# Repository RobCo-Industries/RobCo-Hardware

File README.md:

# RobCo-Hardware

Status: proposals. Nothing here is built, tested or validated on hardware.

This repository holds the board designs for the RobCo suite. Two boards are planned: a terminal controller HAT and a Pip-Boy HAT for the Raspberry Pi. Neither exists yet.

## Boards

| Folder | Board | Status |
|---|---|---|
| `toy/` | Toolchain test: a 3-pin header, a resistor and an LED | Test bed. Schematic, routed board, renders. |
| `toy2/` | Hierarchy test: an expander, a clock and eight LED channels on two sheets | Test bed. Schematic only. |
| `terminal-controller/` | Terminal controller HAT | Schematic drawn, ERC clean. The parts do not fit the HAT yet. See its [README](terminal-controller/README.md). |
| `pipboy-hat/` | Pip-Boy HAT: display, keys, dial, speaker, clock and holotape slot for a Pi Zero | Schematic drawn, ERC clean. Holotape slot added to the spec and schematic. Board not started. See its [README](pipboy-hat/README.md). |

The terminal controller spec is in [terminal-controller/spec/SPEC.md](terminal-controller/spec/SPEC.md), with its bring-up checklist in [BRINGUP.md](terminal-controller/spec/BRINGUP.md) and its header map in [pins.yaml](terminal-controller/spec/pins.yaml). The Pip-Boy HAT spec is in [pipboy-hat/spec/SPEC.md](pipboy-hat/spec/SPEC.md), with [BRINGUP.md](pipboy-hat/spec/BRINGUP.md) and [pins.yaml](pipboy-hat/spec/pins.yaml).

## Safety

The boards are for low voltage only, 5 to 24 V. They never switch mains. Mains loads need an external, rated relay module.

## Tools

- KiCad 10.0.8 with `kicad-cli`. On macOS the scripts find it in `/Applications/KiCad`. On Linux they look in `/usr/bin` and `/usr/share/kicad`.
- The Python that ships with KiCad. It can import `pcbnew`, which the board generator needs.
- Python 3.9 or later with `pytest` for the tests. `tools/build.sh test` makes a venv under `build/`.
- RobCo-Core, for the pin check. Set `ROBCO_BOARD_SUPPORT` to the path of its `docs/spec/BOARD_SUPPORT.md`. The script also finds a RobCo-Core clone next to this one, or two levels up from a worktree.

## Generate, check and export a board

```sh
tools/build.sh gen toy     # rewrite toy/kicad/ from toy/gen/
tools/build.sh check toy   # regen-diff, ERC, pin check, DRC
tools/build.sh out toy     # PDF, SVG, netlist, BOM, renders, gerbers, drill
tools/build.sh test        # Python tests
```

Every output goes to `build/<board>/`. Run `tools/build.sh` with no command for the full list and the variables it reads.

`check` fails when:

- the committed KiCad files differ from a fresh generation,
- ERC finds any violation,
- a header pin in the netlist differs from `spec/pins.yaml`, or `pins.yaml` gives a GPIO another use than the software,
- the pin table in `spec/SPEC.md` differs from the one `tools/gen_pin_table.py` writes from `pins.yaml`,
- a board whose `board.env` names netlist tests with `NETTEST` fails one of them,
- DRC finds a violation, on a board whose `board.env` says `ROUTED=yes`. On other boards DRC only writes a report.

A board with no board file yet is checked as a schematic. `check` runs the regen-diff, ERC and the pin checks, and prints a line for each step it skips. A board with no generator yet gets the pin checks only. When the owner routes a board, `board.env` says `OWNER_ROUTED=yes`. The committed board file is then the source: `gen` and the regen-diff cover the schematic and project files only.

## Where the PDFs and renders come from

Nobody commits them. CI builds them on every push and pull request and keeps them as run artifacts: `toy-outputs` holds the schematic PDFs, SVGs, netlists, BOMs and reports of both toys and the fab files of `toy/`, and `toy-renders` holds the 3D pictures. Locally, `tools/build.sh out` writes the same files.

The render job runs in `kicad/kicad:10.0-full`, the image with the stock 3D models. `kicad/kicad:10.0` has none. Before it renders, `tools/check_models.py` lists every model the board file references and prints a `::warning::` line for each one it cannot find, with the count.

## Layout

```
lib/       own symbols and footprints, shared by the boards
tools/     generators, checks and build script
tests/     pytest for the tools
toy/       the toolchain test board
  spec/    pins.yaml
  gen/     circuit.py writes the schematic, board.py writes the board
  kicad/   generated KiCad files, committed
toy2/      the hierarchy test, same shape, no board file
terminal-controller/
  spec/    SPEC.md, BRINGUP.md, pins.yaml
  gen/     circuit.py and one module per sheet in sheets/
  kicad/   generated KiCad files, committed
pipboy-hat/
  spec/    SPEC.md, BRINGUP.md, pins.yaml
  gen/     circuit.py and one module per sheet in sheets/
  kicad/   generated KiCad files, committed
```

See [CONTRIBUTING.md](CONTRIBUTING.md) for the conventions and [LICENSE.md](LICENSE.md) for the licences.

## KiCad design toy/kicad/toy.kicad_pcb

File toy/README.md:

# Toy board

The toolchain test board: a 3-pin header, R1 and D1. `tools/build.sh pictures toy` exports these pictures from `kicad/toy.kicad_pcb`.

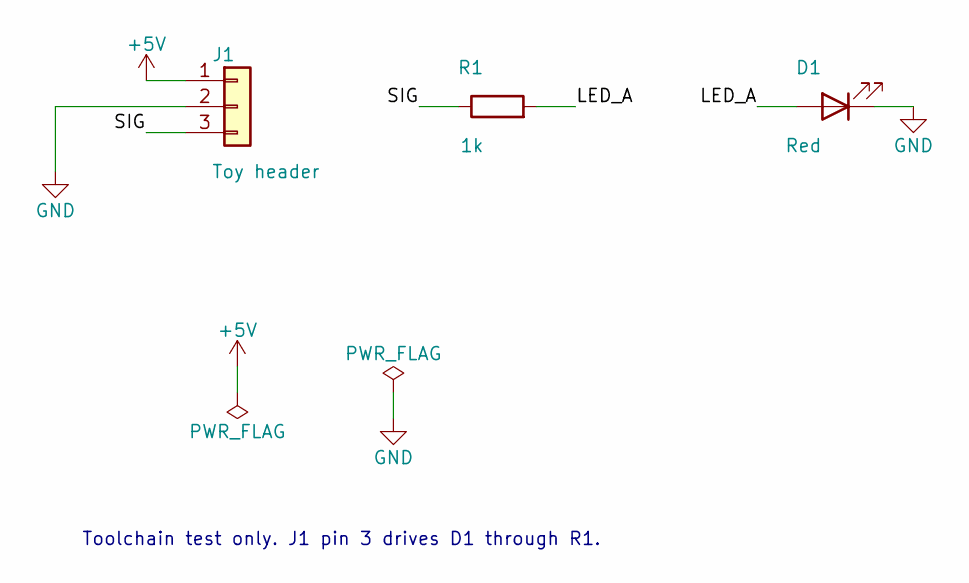
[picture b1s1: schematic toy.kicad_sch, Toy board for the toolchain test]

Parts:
D1: Red; LED_0805_2012Metric
J1: Toy header; PinHeader_1x03_P2.54mm_Vertical
R1: 1k; R_0805_2012Metric

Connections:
+5V: J1.1
/LED_A: D1.2 (A), R1.2
/SIG: J1.3, R1.1
GND: D1.1 (K), J1.2

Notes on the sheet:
Toolchain test only. J1 pin 3 drives D1 through R1.

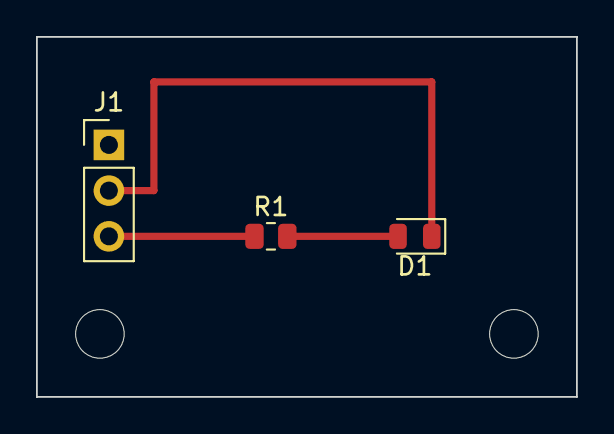
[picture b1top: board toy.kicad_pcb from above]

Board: 2 copper layers, 30.0 x 20.0 mm, 5 parts (0 on the bottom side), 3 nets.

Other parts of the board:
H1, H2: MountingHole_2.7mm_M2.5
